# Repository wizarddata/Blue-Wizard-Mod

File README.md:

# Blue Wizard Mod

This is an open source wireless controller for the Kinesis Advantage and Advantage 2 (see below) line of keyboards using the BlueMicro firmware.

Firmware can be found here. https://github.com/wizarddata/BlueMicro_BLE/tree/blue-wizard-working

For now, use the fork linked above to make any layout changes and utilize the adafruit nrf52832 BSP.

Gerbers and BOM are available if you'd like to build your own!

You will need some additional hardware to make your board functional. Links are provided below for guidance:

1) Latching/Toggle/Rocker panel mount switch for power, or bridge J14 pins for always on. 

 https://www.sparkfun.com/products/11138

2) USB-C panel mount extension.
 
 https://www.amazon.com/dp/B08169ZB5C/ref=cm_sw_r_cp_api_glt_fabc_G1MT1V5PB9B76P2SWG2N?_encoding=UTF8&psc=1
 https://www.sparkfun.com/products/15455  
 
3) Momentary panel mount switch for reset (optional, reset switch is onboard).

 https://www.sparkfun.com/products/11995

4) LiPo battery.

 https://www.sparkfun.com/products/13855

***Advantage 2 Troubleshooting***  
Some keyboards experience intermittent joined activations on function keys. Installing a jumper wire from the negative battery connection to the ground pin of the 3.3v regulator can help resolve this issue. The necessary wire is pictured here:  

Some users have reported F1 simultateously triggering F2. A 10k resistor between the pins indicated here will resolve this.

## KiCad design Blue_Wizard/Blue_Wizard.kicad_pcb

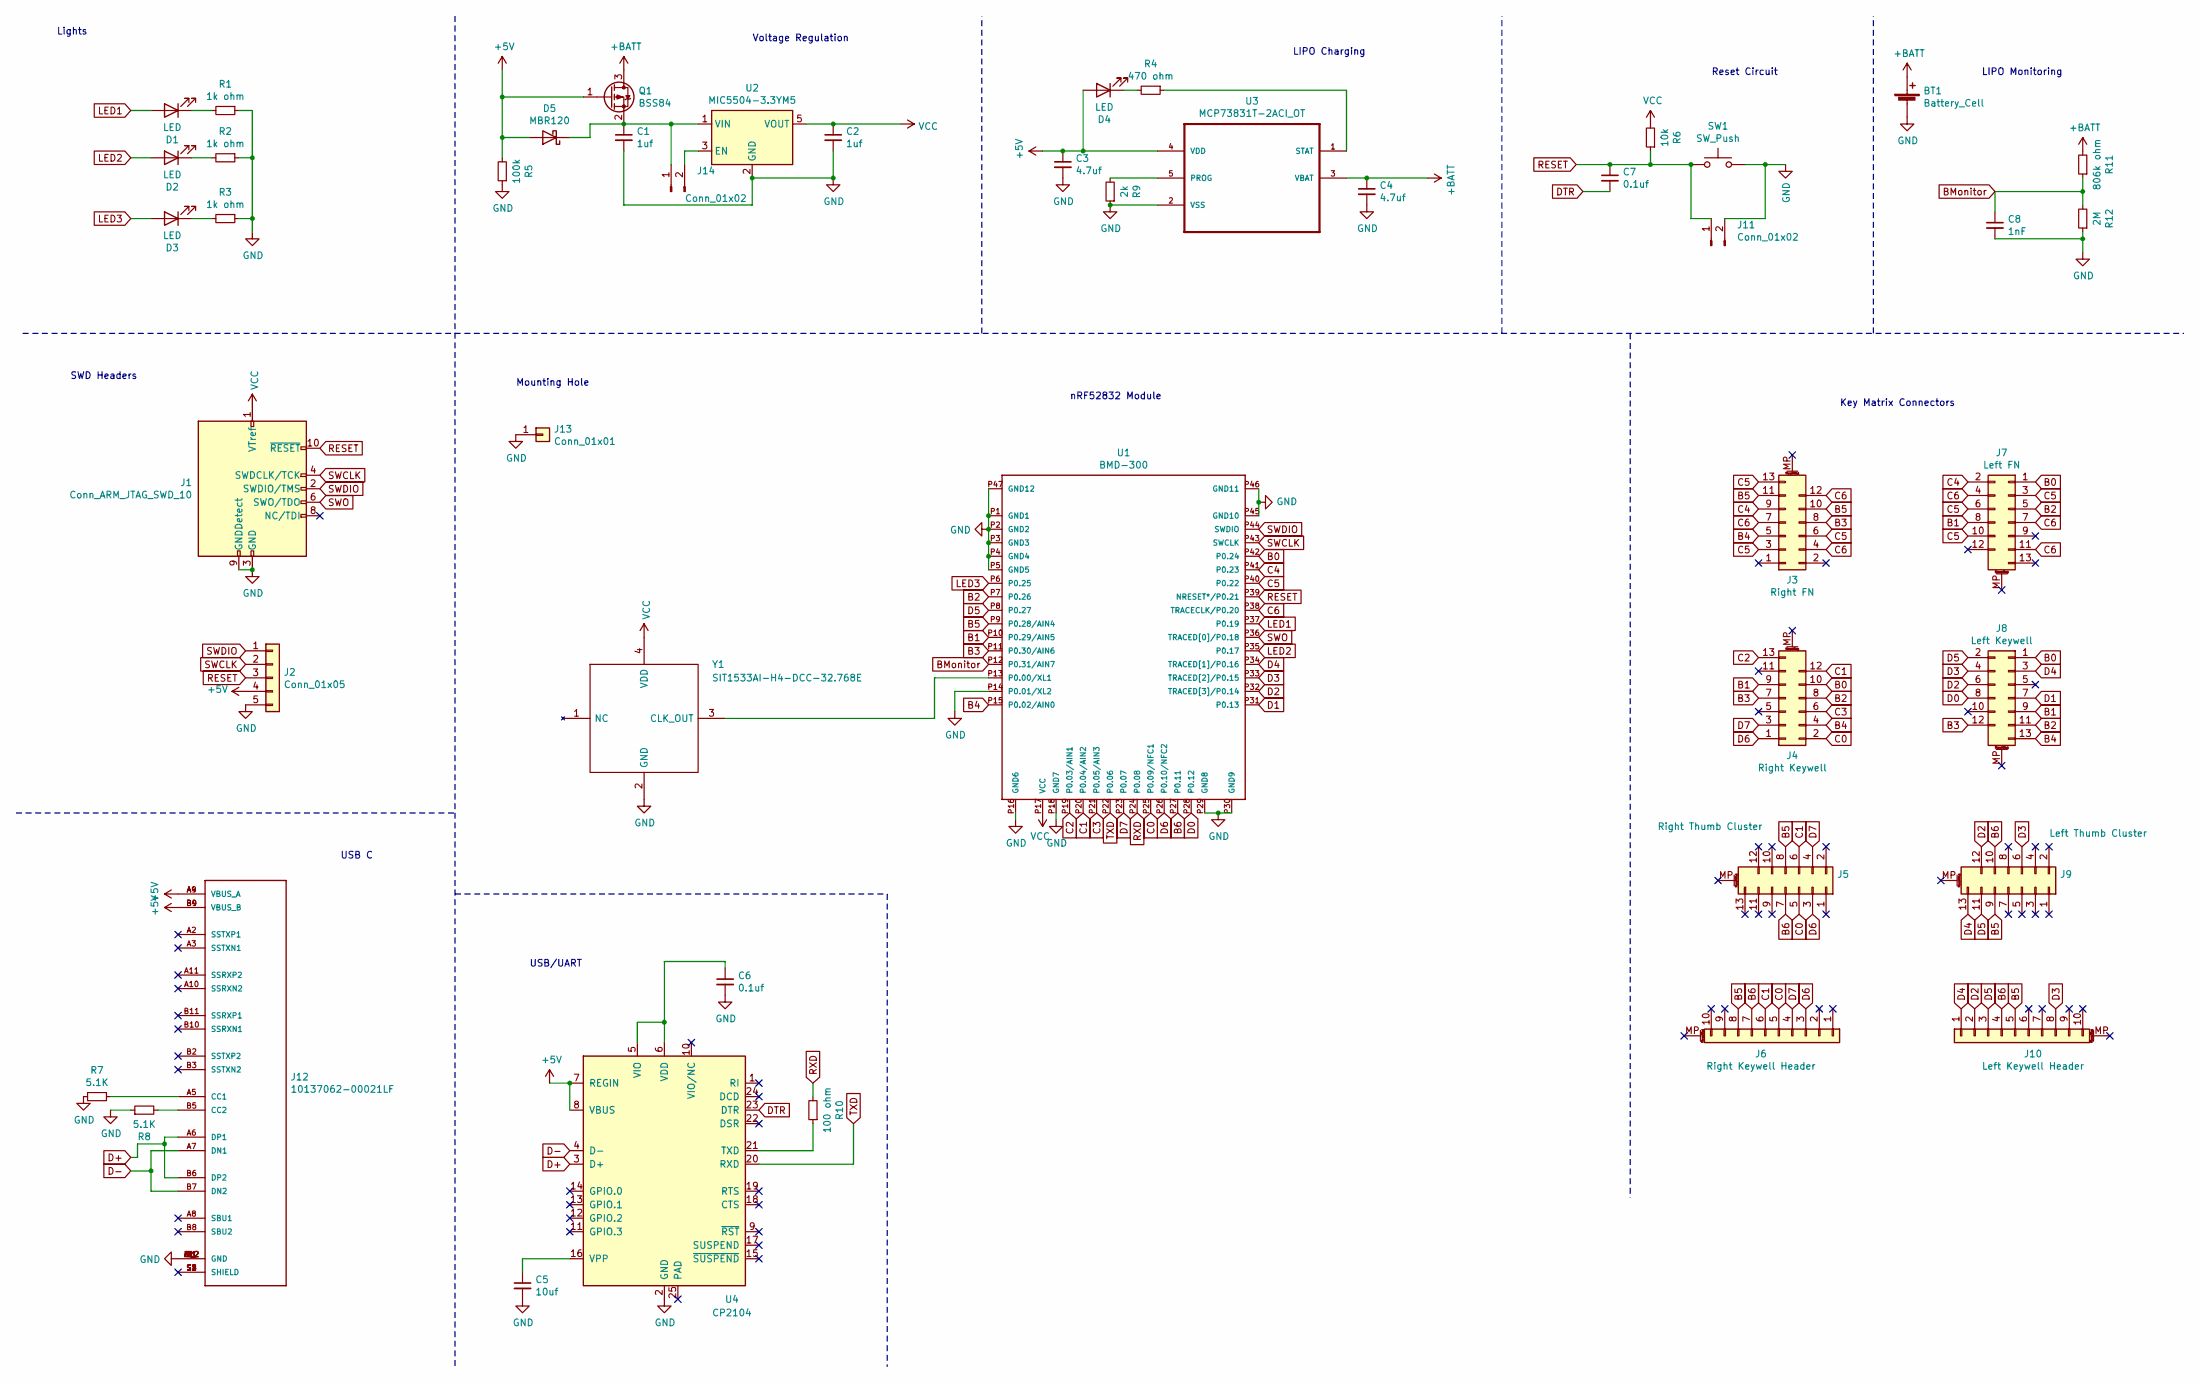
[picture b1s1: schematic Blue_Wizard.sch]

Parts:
BT1: Battery_Cell; PinHeader_1x02_P2.54mm_Vertical
C1, C2: 1uf; C_0805_2012Metric
C3, C4: 4.7uf; C_0805_2012Metric
C5: 10uf; C_0805_2012Metric
C6, C7: 0.1uf; C_0805_2012Metric
C8: 1nF; C_0805_2012Metric
D1, D2, D3, D4: LED; LED_D3.0mm_Clear
D5: MBR120; D_SOD-123F
J1: Conn_ARM_JTAG_SWD_10; PinHeader_2x05_P1.27mm_Vertical_SMD
J2: Conn_01x05; PinHeader_1x05_P2.54mm_Vertical
J3: Right FN; Vertical_FRC
J4: Right Keywell; Horizontal_FRC
J5: Right Thumb Cluster; Vertical_FRC
J6: Right Keywell Header; MA10-1
J7: Left FN; Vertical_FRC
J8: Left Keywell; Horizontal_FRC
J9: Left Thumb Cluster; Vertical_FRC
J10: Left Keywell Header; MA10-1
J11, J14: Conn_01x02; PinHeader_1x02_P2.54mm_Vertical
J12: 10137062-00021LF; CONN_10137062-00021LF
J13: Conn_01x01; Mounting Hole
Q1: BSS84; SOT-23
R1, R2, R3: 1k ohm; R_0805_2012Metric
R4: 470 ohm; R_0805_2012Metric
R5: 100k; R_0805_2012Metric
R6: 10k; R_0805_2012Metric
R7, R8: 5.1K; R_0805_2012Metric
R9: 2k; R_0805_2012Metric
R10: 100 ohm; R_0805_2012Metric
R11: 806k ohm; R_0805_2012Metric
R12: 2M; R_0805_2012Metric
SW1: SW_Push; SW_PTS526_SM08_SMTR2_LFS
U1: BMD-300
U2: MIC5504-3.3YM5; SOT-23-5
U3: MCP73831T-2ACI_OT; SOT95P280X145-5N
U4: CP2104; QFN-24-1EP_4x4mm_P0.5mm_EP2.6x2.6mm
Y1: SIT1533AI-H4-DCC-32.768E; SIT1533AIH4DCC32768E; Mouser Part Number 788-1533AIH4DCC32.76

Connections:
+5V: C3.1, D4.2 (A), D5.2 (A), J2.4, J12.A4 (VBUS_A), J12.A9 (VBUS_A), J12.B4 (VBUS_B), J12.B9 (VBUS_B), Q1.1 (G), R5.2, U3.4 (VDD), U4.7 (REGIN), U4.8 (VBUS)
+BATT: BT1.1 (+), C4.1, Q1.3 (D), R11.2, U3.3 (VBAT)
B0: J4.10, J7.1, J8.1, U1.P42 (P0.24)
B1: J4.9, J7.8, J8.9, U1.P10 (P0.29/AIN5)
B2: J4.8, J7.5, J8.11, U1.P7 (P0.26)
B3: J3.8, J4.7, J8.12, U1.P11 (P0.30/AIN6)
B4: J3.5, J4.4, J8.13, U1.P15 (P0.02/AIN0)
B5: J3.10, J3.11, J5.8, J6.8, J9.9, J10.5, U1.P9 (P0.28/AIN4)
B6: J5.7, J6.7, J9.10, J10.4, U1.P27 (P0.11)
BMonitor: C8.1, R11.1, R12.2, U1.P12 (P0.31/AIN7)
C0: J4.2, J5.5, J6.5, U1.P25 (P0.09/NFC1)
C1: J4.12, J5.6, J6.6, U1.P20 (P0.04/AIN2)
C2: J4.13, U1.P19 (P0.03/AIN1)
C3: J4.6, U1.P21 (P0.05/AIN3)
C4: J3.9, J7.2, U1.P41 (P0.23)
C5: J3.3, J3.6, J3.13, J7.3, J7.6, J7.10, U1.P40 (P0.22)
C6: J3.4, J3.7, J3.12, J7.4, J7.7, J7.11, U1.P38 (TRACECLK/P0.20)
D0: J8.8, U1.P28 (P0.12)
D1: J8.7, U1.P31 (P0.13)
D2: J8.6, J9.12, J10.2, U1.P32 (TRACED[3]/P0.14)
D3: J8.4, J9.6, J10.8, U1.P33 (TRACED[2]/P0.15)
D4: J8.3, J9.13, J10.1, U1.P34 (TRACED[1]/P0.16)
D5: J8.2, J9.11, J10.3, U1.P8 (P0.27)
D6: J4.1, J5.3, J6.3, U1.P26 (P0.10/NFC2)
D7: J4.3, J5.4, J6.4, U1.P23 (P0.07)
D+: J12.A6 (DP1), J12.B6 (DP2), U4.3 (D+)
D-: J12.A7 (DN1), J12.B7 (DN2), U4.4 (D-)
DTR: C7.2, U4.23 (DTR)
GND: BT1.2 (-), C1.2, C2.2, C3.2, C4.2, C5.2, C6.2, C8.2, J1.3 (GND), J1.5 (GND), J1.9 (GNDDetect), J2.5, J11.2, J12.A1 (GND), J12.A12 (GND), J12.B1 (GND), J12.B12 (GND), J13.1, R1.1, R2.1, R3.1, R5.1, R7.2, R8.1, R9.1, R12.1, SW1.2, U1.P1 (GND1), U1.P2 (GND2), U1.P3 (GND3), U1.P4 (GND4), U1.P5 (GND5), U1.P14 (P0.01/XL2), U1.P16 (GND6), U1.P18 (GND7), U1.P29 (GND8), U1.P30 (GND9), U1.P45 (GND10), U1.P46 (GND11), U1.P47 (GND12), U2.2 (GND), U3.2 (VSS), U4.2 (GND), Y1.2 (GND)
LED1: D1.2 (A), U1.P37 (P0.19)
LED2: D2.2 (A), U1.P35 (P0.17)
LED3: D3.2 (A), U1.P6 (P0.25)
unnamed: C1.1, D5.1 (K), J14.1, Q1.2 (S), U2.1 (VIN)
unnamed: C5.1, U4.16 (VPP)
unnamed: C6.1, U4.5 (VIO), U4.6 (VDD)
unnamed: D1.1 (K), R1.2
unnamed: D2.1 (K), R2.2
unnamed: D3.1 (K), R3.2
unnamed: D4.1 (K), R4.2
unnamed: J12.A5 (CC1), R7.1
unnamed: J12.B5 (CC2), R8.2
unnamed: J12.S1 (SHIELD), J12.S2 (SHIELD), J12.S3 (SHIELD), J12.S4 (SHIELD)
unnamed: J14.2, U2.3 (EN)
unnamed: R4.1, U3.1 (STAT)
unnamed: R9.2, U3.5 (PROG)
unnamed: R10.1, U4.21 (TXD)
unnamed: U1.P13 (P0.00/XL1), Y1.3 (CLK_OUT)
RESET: C7.1, J1.10 (~RESET~), J2.3, J11.1, R6.1, SW1.1, U1.P39 (NRESET*/P0.21)
RXD: R10.2, U1.P24 (P0.08)
SWCLK: J1.4 (SWDCLK/TCK), J2.2, U1.P43 (SWCLK)
SWDIO: J1.2 (SWDIO/TMS), J2.1, U1.P44 (SWDIO)
SWO: J1.6 (SWO/TDO), U1.P36 (TRACED[0]/P0.18)
TXD: U1.P22 (P0.06), U4.20 (RXD)
VCC: C2.1, J1.1 (VTref), R6.2, U1.P17 (VCC), U2.5 (VOUT), Y1.4 (VDD)

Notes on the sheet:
SWD Headers
Lights
Voltage Regulation
LIPO Charging
Reset Circuit
LIPO Monitoring
Key Matrix Connectors
Mounting Hole
USB/UART
USB C
nRF52832 Module

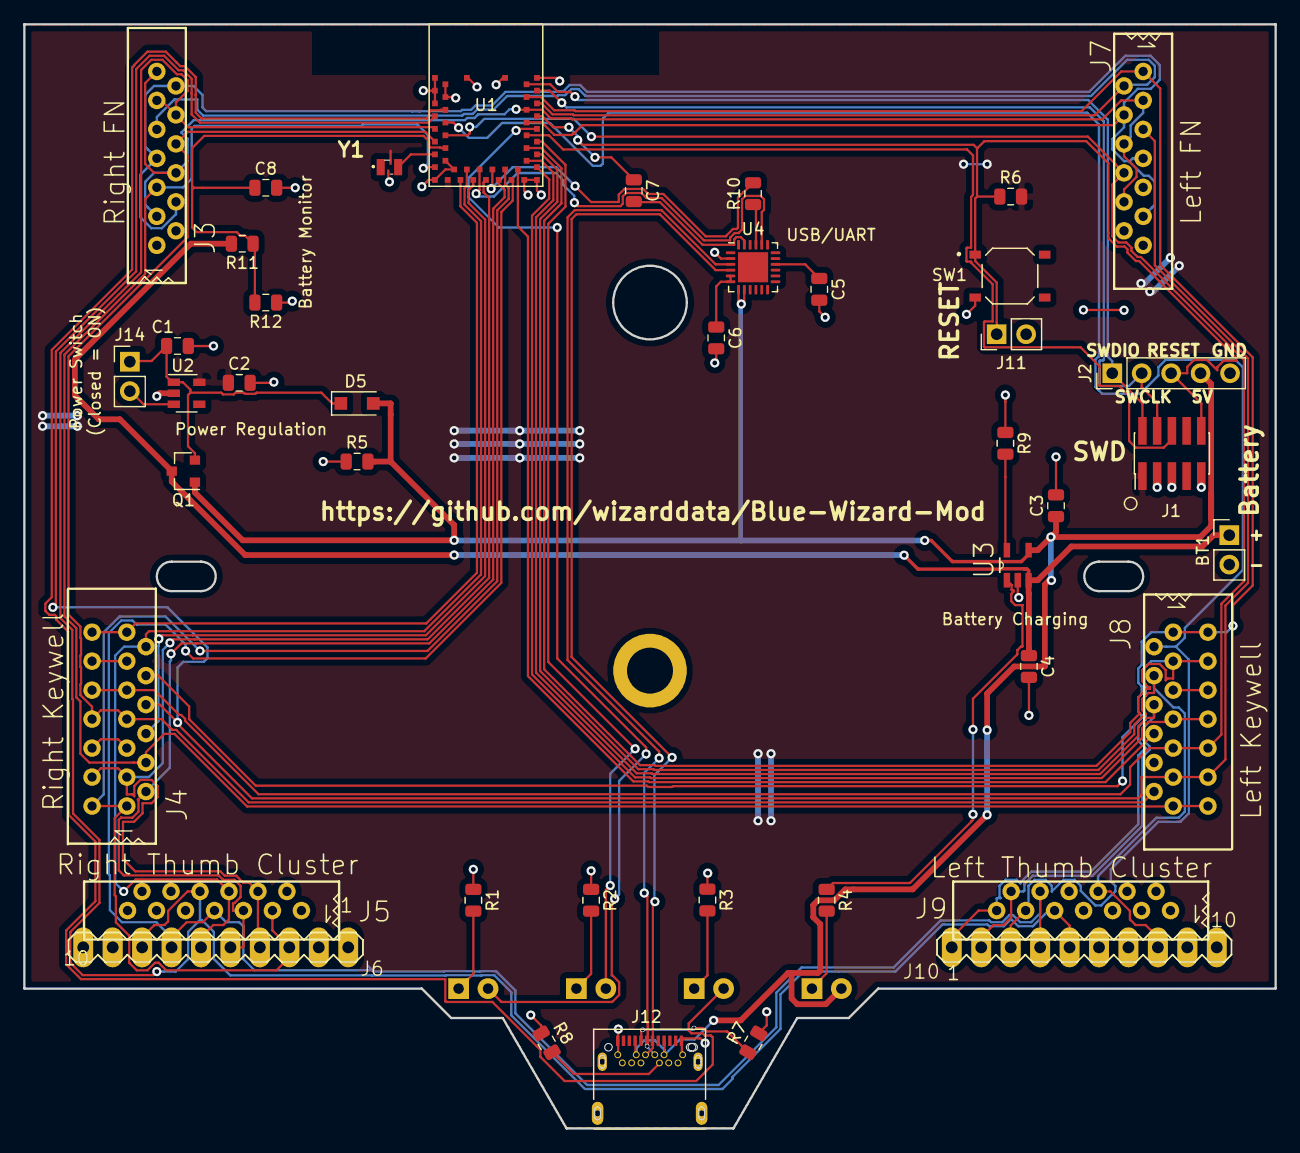
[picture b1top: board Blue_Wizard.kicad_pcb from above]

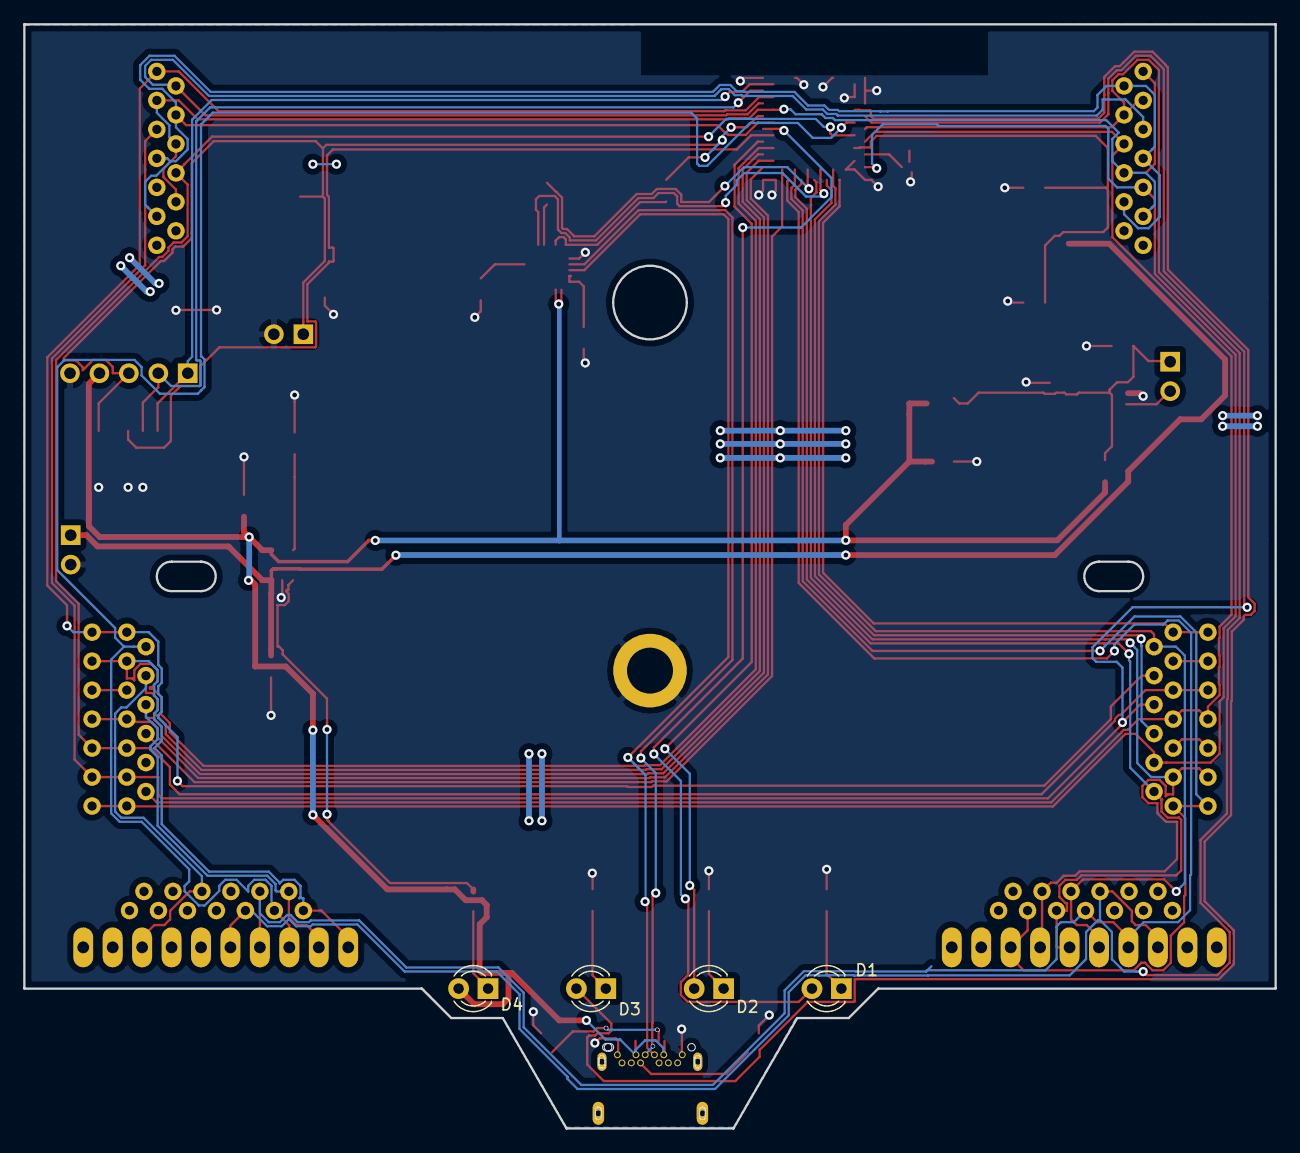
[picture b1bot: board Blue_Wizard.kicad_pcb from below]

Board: 2 copper layers, 108.0 x 95.2 mm, 47 parts (4 on the bottom side), 54 nets.

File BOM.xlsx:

| Mfr. # | Description | Order Qty.
C5 | C0805C106K9PACTU | Multilayer Ceramic Capacitors MLCC - SMD/SMT 6.3volts 10uF X5R 10% | 1
C6, C7 | 885012207098 | Multilayer Ceramic Capacitors MLCC - SMD/SMT WCAP-CSGP 0.1uF 0805 10% 50V MLCC | 2
C8 | 885342207008 | Multilayer Ceramic Capacitors MLCC - SMD/SMT WCAP-CSMH 250V 1000pF 0805 10% | 1
R1, R2, R3 | CRCW08051K00FKEAC | Thick Film Resistors - SMD 1/8Watt 1Kohms 1% Commercial Use | 3
R9 | CR0805-FX-2101ELF | Thick Film Resistors - SMD 2.1K 1% | 1
R11 | CR0805-FX-8063ELF | Thick Film Resistors - SMD 806K 1% | 1
R12 | WCR0805LF2004FPLT | Thick Film Resistors - SMD 2M OHM 1% | 1
U4 | CP2104-F03-GM | I/O Controller Interface IC USB to UART Bridge QFN24 | 1
Y1 | SiT1533AI-H4-DCC-32.768E | Standard Clock Oscillators 32.768KHz R2R LVCMOS -40 to 85C 100ppm | 1
R10 | CRCW0805100RFKEA | Thick Film Resistors - SMD 1/8watt 100ohms 1% 100ppm | 1
C3, C4 | 0805X475M250CT | Multilayer Ceramic Capacitors MLCC - SMD/SMT 0805 MLCC X5R 4.7 uF +/- 20% 25 V 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 | 2
D5 | MBR120ESFT3G | Schottky Diodes & Rectifiers 1A 20V | 1
Q1 | BSS84 | MOSFET SOT-23 P-CH ENHANCE | 1
C1, C2 | 885012207078 | Multilayer Ceramic Capacitors MLCC - SMD/SMT WCAP-CSGP 1uF 0805 10% 25V MLCC | 2
R6 | CRCW080510K0FKEAC | Thick Film Resistors - SMD 1/8Watt 10Kohms 1% Commercial Use | 1
R5 | CRCW0805100KJNEAC | Thick Film Resistors - SMD 1/8Watt 100Kohms 5% Commercial Use | 1
R7, R8 | CRCW08055K10FKEA | Thick Film Resistors - SMD 1/8watt 5.1Kohms 1% 100ppm | 2
D1-D4 | LTL-4231N | Standard LEDs - Through Hole Green Diffused | 4
J12 | 10137062-00021LF | USB Connectors USB 3.1 RECE. CONN. Gen 1 | 1
SW1 | PTS526 SM08 SMTR2 LFS | Tactile Switches 50mA 12VDC, 5.2x5.2mm, 0.8mm H, 160gf, G leads, No ground pin,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 | 1
J1 | 20021121-00010C4LF | Headers & Wire Housings 1.27x1.27mm BTB, Hdr Unshrd, SMT, 10 Pos | 1
U3 | MCP73831T-2ACI/OT | Battery Management Charge mgnt contr | 1
U1 | BMD-300-A-R | Bluetooth Modules (802.15.1) Bluetooth Module Low Energy 5.0 | 1
R4 | RK73B2ATTD471J | Thick Film Resistors - SMD 1/4watts 470ohms 5% | 1
U2 | MIC5504-3.3YM5-TR | LDO Voltage Regulators Single 300mA LDO | 1
J4, J8 | 39-53-2134 | Right Angle FFC/FPC 13 POS Through Hole | 0-2 |  | These connectors vary depending on your advantage model.
J3, J4, J5, J7, J8, J9 | 39-53-2135 | Vertical FFC/FPC 13 POS Through Hole | 2-6

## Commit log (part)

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2020-07-25 Update README.md
    Updated to reflect functioning prototype.
2020-08-03 moved .gitignore
2020-08-03 housekeeping
2020-08-07 Rev 0 in progress
2020-08-13 pre-final
2020-08-15 Generated Rev 0 gerbers
2020-08-25 readme update
2020-09-06 Final Gerbers and BOM
2020-09-11 Rev 0a board complete
2020-11-30 Updated front silkscreen and removed KiCad project
2020-11-30 formatting
2020-11-30 Contact info
2020-11-30 Readme format
2020-11-30 Cleaned up KiCad project
2020-11-30 Edited README.md
2020-12-01 Update README.md
    Added links and explanation for additional hardware.
